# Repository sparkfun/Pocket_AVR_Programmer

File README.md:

Pocket AVR Programmer
=====================

[  
*Pocket AVR Programmer (PGM-09825)*](https://www.sparkfun.com/products/9825)

This is a simple to use USB AVR programmer, that works with ATmega168 and ATmega328 and should work well
with all the AVR micros supported by AVRDUDE.

Repository Contents
-------------------
* **/Enclosure** - 3D model of enclosure for this (.stl).
* **/Drivers** - Windows 7 drivers for use with this programmer. 
* **/Firmware** - Firmware that ships on the Pocket AVR Programmer.
* **/Hardware** - All Eagle design files (.brd, .sch).

Documentation
--------------
* **[Hookup Guide](https://learn.sparkfun.com/tutorials/pocket-avr-programmer-hookup-guide)** - Basic hookup guide for the Pocket AVR Programmer. 
* **[Installing an Arduino Bootloader](https://learn.sparkfun.com/tutorials/installing-an-arduino-bootloader)**  - Example of installing an Arduino bootloader on an Atmega328P-based microcontrollers (i.e. Arduino Uno and RedBoard Programmed with Arduino) through the Arduino IDE and command line using avrdude.

License Information
-------------------
The hardware is released under [Creative Commons Share-alike 3.0](http://creativecommons.org/licenses/by-sa/3.0/).
The firmware is based off of:
* [USBtiny](http://dicks.home.xs4all.nl/avr/usbtiny/index.html) by Dick Streefland
* [USBtinyISP](http://www.ladyada.net/make/usbtinyisp/) by Limor Fried and is a collaboration with Limor Fried currently.

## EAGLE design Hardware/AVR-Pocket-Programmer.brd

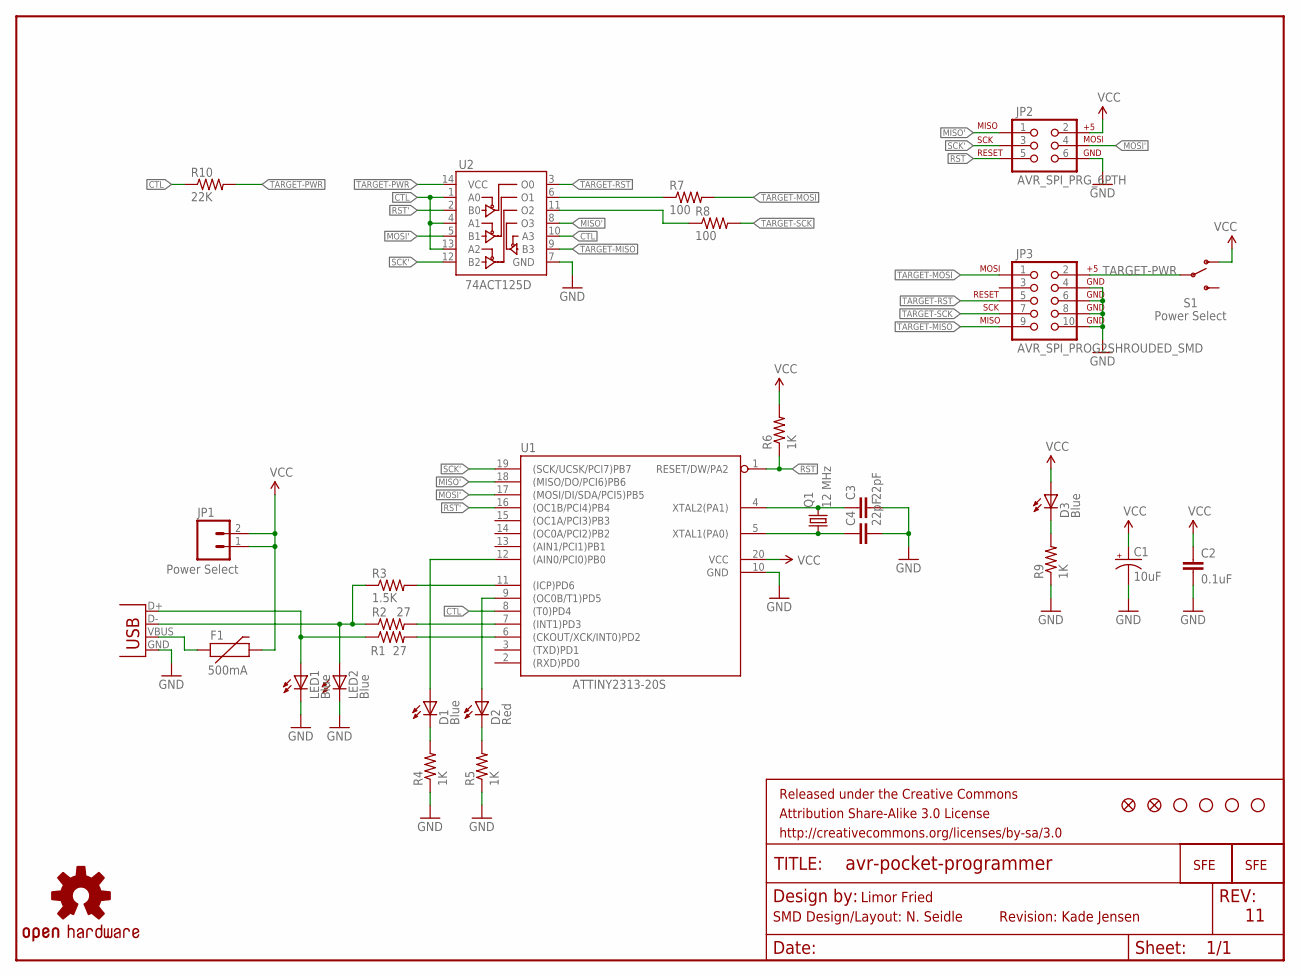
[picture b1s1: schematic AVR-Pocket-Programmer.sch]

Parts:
C1: 10uF; EIA3216
C2: 0.1uF; 0603-CAP
C3, C4: 22pF; 0603-CAP
D1, D3: Blue; LED-0603
D2: Red; LED-0603
F1: 500mA; PTC-1206-WIDE
FRAME1: FRAME-LETTER; CREATIVE_COMMONS
JP1: Power Select; 1X02
JP2: AVR_SPI_PRG_6PTH; 2X3
JP3: AVR_SPI_PROG2SHROUDED_SMD; 2X5-SHROUDED_SMD
LED1, LED2: Blue; LED-0603
LOGO1: OSHW-LOGOM; OSHW-LOGO-M
Q1: 12 MHz; CRYSTAL-SMD-5X3
R1, R2: 27; 0603-RES
R3: 1.5K; 0603-RES
R4, R5, R6, R9: 1K; 0603-RES
R7, R8: 100; 0603-RES
R10: 22K; 0603-RES
S1: Power Select; AYZ0202
U1: ATTINY2313-20S; SO20L
U2: 74ACT125D; SO014
U$1, U$3, U$4, U$5: STAND-OFF
U$2: LOGO-SFESK; SFE-LOGO-FLAME
U$6, U$7: FIDUCIAL1X2; FIDUCIAL-1X2
U$8: LOGO-SFENEW; SFE-NEW-WEBLOGO
X2: USBSMD; USB-MINIB

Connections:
CTL: R10.1, U1.8 ((T0)PD4), U2.1 (A0), U2.4 (A1), U2.10 (A3), U2.13 (A2)
D+: LED1.A, R1.1, X2.D+
D-: LED2.A, R2.1, R3.1, X2.D-
GND: C1.C (-), C2.2, C3.2, C4.2, JP2.6, JP3.4, JP3.6, JP3.8, JP3.10, LED1.C, LED2.C, R4.1, R5.1, R9.1, U1.10 (GND), U2.7 (GND), X2.GND
MISO': JP2.1, U1.18 ((MISO/DO/PCI6)PB6), U2.8 (O3)
MOSI': JP2.4, U1.17 ((MOSI/DI/SDA/PCI5)PB5), U2.5 (B1)
unnamed: R3.2, U1.11 ((ICP)PD6)
unnamed: D2.A, U1.9 ((OC0B/T1)PD5)
unnamed: D3.C, R9.2
unnamed: F1.1, X2.VBUS
unnamed: C3.1, Q1.3 (2), U1.4 (XTAL2(PA1))
unnamed: C4.1, Q1.1, U1.5 (XTAL1(PA0))
unnamed: D1.A, U1.12 ((AIN0/PCI0)PB0)
unnamed: D1.C, R4.2
unnamed: D2.C, R5.2
unnamed: R7.1, U2.6 (O1)
unnamed: R8.1, U2.11 (O2)
PD+: R1.2, U1.6 ((CKOUT/XCK/INT0)PD2)
PD-: R2.2, U1.7 ((INT1)PD3)
RST: JP2.5, R6.1, U1.1 (RESET/DW/PA2)
RST': U1.16 ((OC1B/PCI4)PB4), U2.2 (B0)
SCK': JP2.3, U1.19 ((SCK/UCSK/PCI7)PB7), U2.12 (B2)
TARGET-MISO: JP3.9, U2.9 (B3)
TARGET-MOSI: JP3.1, R7.2
TARGET-PWR: JP3.2, R10.2, S1.2, U2.14 (VCC)
TARGET-RST: JP3.5, U2.3 (O0)
TARGET-SCK: JP3.7, R8.2
VCC: C1.A (+), C2.1, D3.A, F1.2, JP1.1, JP1.2, JP2.2, R6.2, S1.1 (O), U1.20 (VCC)

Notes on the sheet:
Limor Fried
SMD Design/Layout: N. Seidle
Revision: Kade Jensen

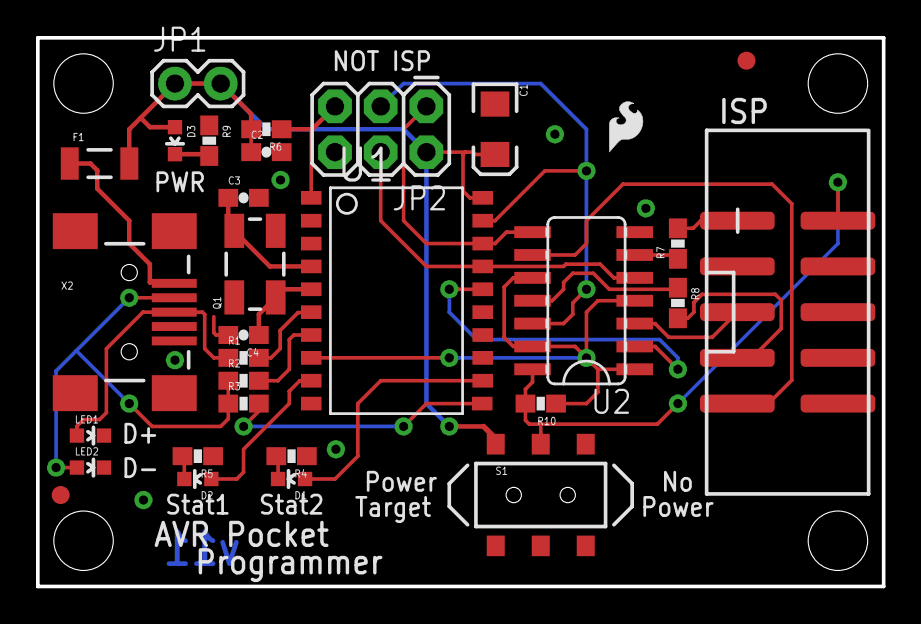
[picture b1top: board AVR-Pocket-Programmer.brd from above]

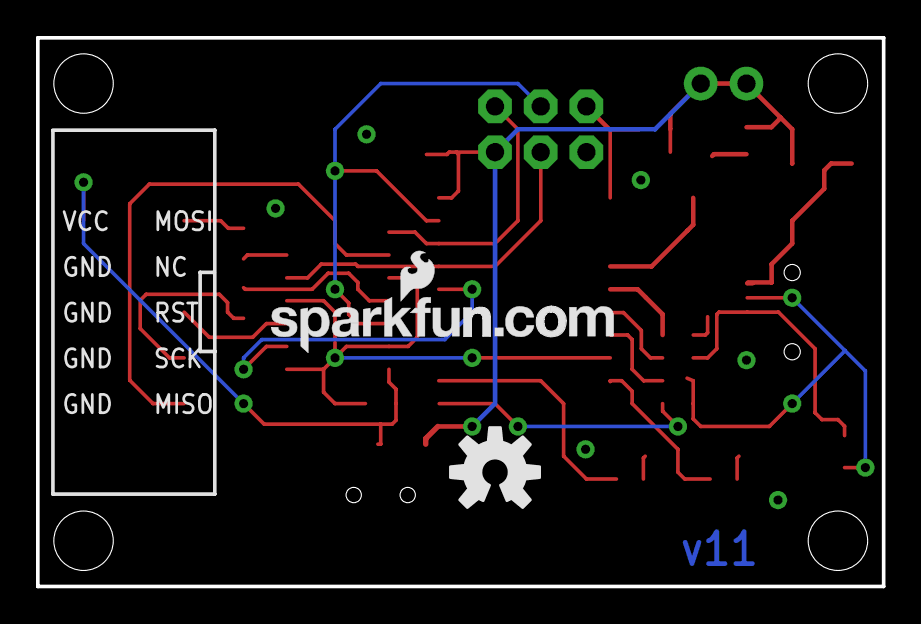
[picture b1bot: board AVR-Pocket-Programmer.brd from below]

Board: 2 copper layers, 47.0 x 30.5 mm, 38 parts (2 on the bottom side), 28 nets.

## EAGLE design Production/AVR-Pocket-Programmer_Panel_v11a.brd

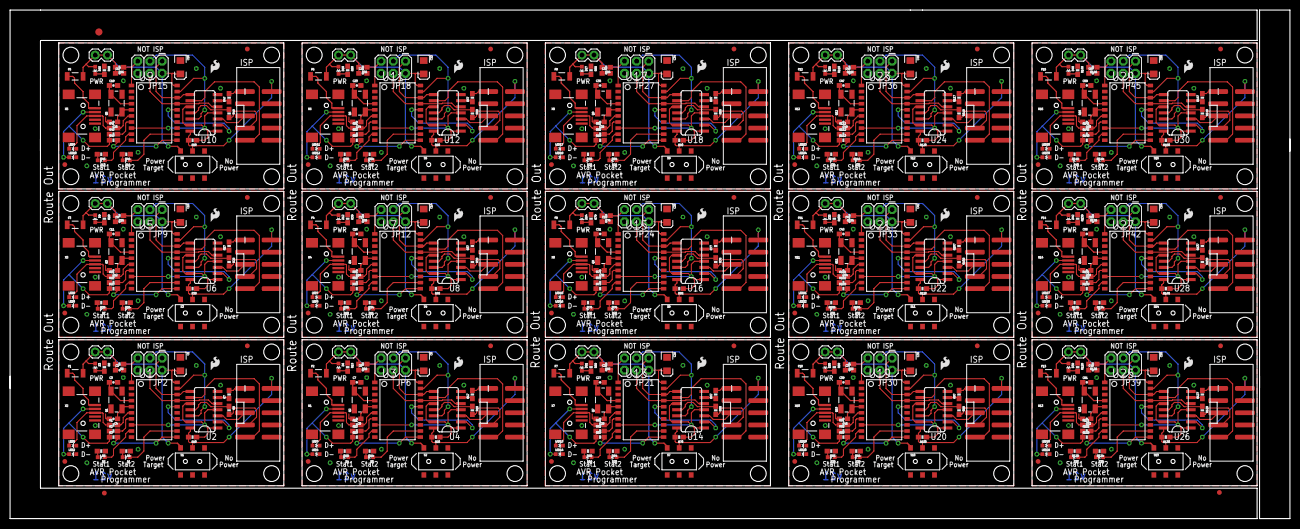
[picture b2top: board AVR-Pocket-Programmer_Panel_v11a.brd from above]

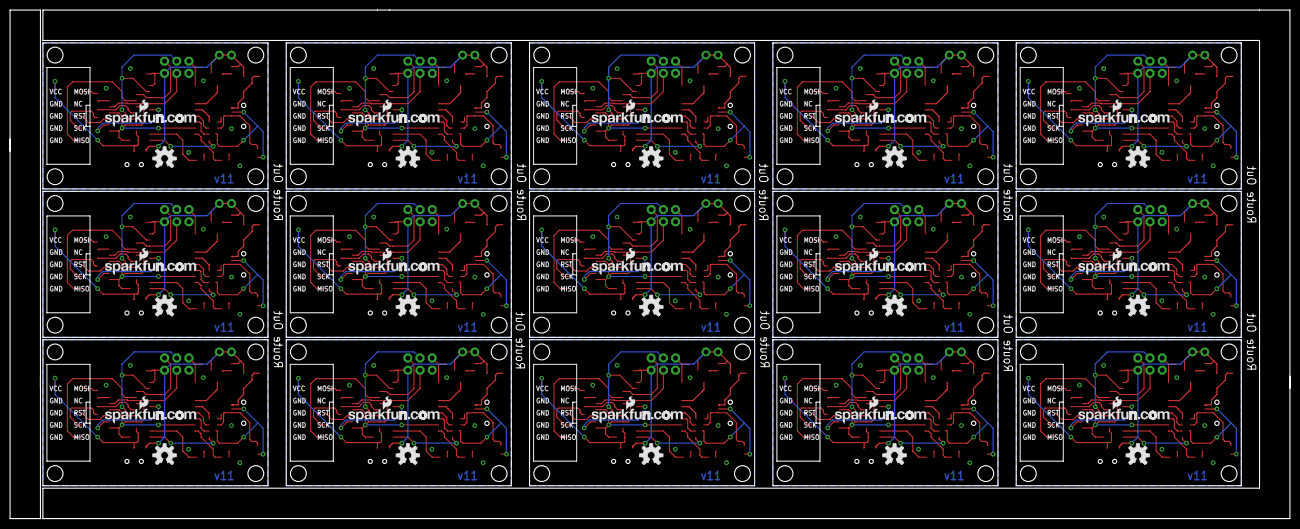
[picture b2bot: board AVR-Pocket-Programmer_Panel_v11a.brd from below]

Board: 2 copper layers, 267.2 x 106.2 mm, 558 parts (30 on the bottom side), 420 nets.

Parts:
C1, C6, C10, C14, C18, C22, C26, C30, C34, C38, C42, C46, C50, C54, C58: 10uF; EIA3216
C2, C5, C9, C13, C17, C21, C25, C29, C33, C37, C41, C45, C49, C53, C57: 0.1uF; 0603-CAP
C3, C4, C7, C8, C11, C12, C15, C16, C19, C20, C23, C24, C27, C28, C31, C32, C35, C36, C39, C40, C43, C44, C47, C48, C51, C52, C55, C56, C59, C60: 22pF; 0603-CAP
D1, D3, D5, D6, D8, D9, D11, D12, D14, D15, D17, D18, D20, D21, D23, D24, D26, D27, D29, D30, D32, D33, D35, D36, D38, D39, D41, D42, D44, D45: Blue; LED-0603
D2, D4, D7, D10, D13, D16, D19, D22, D25, D28, D31, D34, D37, D40, D43: Red; LED-0603
E$1: FIDUCIAL-1.5X3
E$2, E$7: FIDUCIAL-1X2
F1, F2, F3, F4, F5, F6, F7, F8, F9, F10, F11, F12, F13, F14, F15: 500mA; PTC-1206-WIDE
JP1, JP4, JP7, JP10, JP13, JP16, JP19, JP22, JP25, JP28, JP31, JP34, JP37, JP40, JP43: Power Select; 1X02
JP2, JP6, JP9, JP12, JP15, JP18, JP21, JP24, JP27, JP30, JP33, JP36, JP39, JP42, JP45: AVR_SPI_PRG_6PTH; 2X3
JP3, JP5, JP8, JP11, JP14, JP17, JP20, JP23, JP26, JP29, JP32, JP35, JP38, JP41, JP44: AVR_SPI_PROG2SHROUDED_SMD; 2X5-SHROUDED_SMD
LED1, LED2, LED3, LED4, LED5, LED6, LED7, LED8, LED9, LED10, LED11, LED12, LED13, LED14, LED15, LED16, LED17, LED18, LED19, LED20, LED21, LED22, LED23, LED24, LED25, LED26, LED27, LED28, LED29, LED30: Blue; LED-0603
LOGO1, LOGO2, LOGO3, LOGO4, LOGO5, LOGO6, LOGO7, LOGO8, LOGO9, LOGO10, LOGO11, LOGO12, LOGO13, LOGO14, LOGO15: OSHW-LOGOM; OSHW-LOGO-M
Q1, Q2, Q3, Q4, Q5, Q6, Q7, Q8, Q9, Q10, Q11, Q12, Q13, Q14, Q15: 12 MHz; CRYSTAL-SMD-5X3
R1, R2, R11, R12, R21, R22, R31, R32, R41, R42, R51, R52, R61, R62, R71, R72, R81, R82, R91, R92, R101, R102, R111, R112, R121, R122, R131, R132, R141, R142: 27; 0603-RES
R3, R13, R23, R33, R43, R53, R63, R73, R83, R93, R103, R113, R123, R133, R143: 1.5K; 0603-RES
R4, R5, R6, R9, R14, R15, R16, R19, R24, R25, R26, R29, R34, R35, R36, R39, R44, R45, R46, R49, R54, R55, R56, R59, R64, R65, R66, R69, R74, R75, R76, R79, R84, R85, R86, R89, R94, R95, R96, R99, R104, R105, R106, R109, R114, R115, R116, R119, R124, R125, R126, R129, R134, R135, R136, R139, R144, R145, R146, R149: 1K; 0603-RES
R7, R8, R17, R18, R27, R28, R37, R38, R47, R48, R57, R58, R67, R68, R77, R78, R87, R88, R97, R98, R107, R108, R117, R118, R127, R128, R137, R138, R147, R148: 100; 0603-RES
R10, R20, R30, R40, R50, R60, R70, R80, R90, R100, R110, R120, R130, R140, R150: 22K; 0603-RES
S1, S2, S3, S4, S5, S6, S7, S8, S9, S10, S11, S12, S13, S14, S15: Power Select; AYZ0202
U1, U3, U5, U7, U9, U11, U13, U15, U17, U19, U21, U23, U25, U27, U29: ATTINY2313-20S; SO20L
U2, U4, U6, U8, U10, U12, U14, U16, U18, U20, U22, U24, U26, U28, U30: 74ACT125D; SO014
U$1, U$3, U$4, U$5, U$9, U$10, U$11, U$12, U$17, U$18, U$19, U$20, U$25, U$26, U$27, U$28, U$33, U$34, U$35, U$36, U$41, U$42, U$43, U$44, U$49, U$50, U$51, U$52, U$57, U$58, U$59, U$60, U$65, U$66, U$67, U$68, U$73, U$74, U$75, U$76, U$81, U$82, U$83, U$84, U$89, U$90, U$91, U$92, U$97, U$98, U$99, U$100, U$105, U$106, U$107, U$108, U$113, U$114, U$115, U$116: STAND-OFF
U$2, U$16, U$24, U$32, U$40, U$48, U$56, U$64, U$72, U$80, U$88, U$96, U$104, U$112, U$120: LOGO-SFESK; SFE-LOGO-FLAME
U$6, U$7, U$13, U$14, U$21, U$22, U$29, U$30, U$37, U$38, U$45, U$46, U$53, U$54, U$61, U$62, U$69, U$70, U$77, U$78, U$85, U$86, U$93, U$94, U$101, U$102, U$109, U$110, U$117, U$118: FIDUCIAL1X2; FIDUCIAL-1X2
U$8, U$15, U$23, U$31, U$39, U$47, U$55, U$63, U$71, U$79, U$87, U$95, U$103, U$111, U$119: LOGO-SFENEW; SFE-NEW-WEBLOGO
X1, X2, X3, X4, X5, X6, X7, X8, X9, X10, X11, X12, X13, X14, X15: USBSMD; USB-MINIB

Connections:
CTL: R10.1, U1.8, U2.1, U2.4, U2.10, U2.13
CTL1: R20.1, U3.8, U4.1, U4.4, U4.10, U4.13
CTL2: R30.1, U5.8, U6.1, U6.4, U6.10, U6.13
CTL3: R40.1, U7.8, U8.1, U8.4, U8.10, U8.13
CTL4: R50.1, U9.8, U10.1, U10.4, U10.10, U10.13
CTL5: R60.1, U11.8, U12.1, U12.4, U12.10, U12.13
CTL6: R70.1, U13.8, U14.1, U14.4, U14.10, U14.13
CTL7: R80.1, U15.8, U16.1, U16.4, U16.10, U16.13
CTL8: R90.1, U17.8, U18.1, U18.4, U18.10, U18.13
CTL9: R100.1, U19.8, U20.1, U20.4, U20.10, U20.13
CTL10: R110.1, U21.8, U22.1, U22.4, U22.10, U22.13
CTL11: R120.1, U23.8, U24.1, U24.4, U24.10, U24.13
CTL12: R130.1, U25.8, U26.1, U26.4, U26.10, U26.13
CTL13: R140.1, U27.8, U28.1, U28.4, U28.10, U28.13
CTL14: R150.1, U29.8, U30.1, U30.4, U30.10, U30.13
D+: LED1.A, R1.1, X2.D+
D+1: LED3.A, R11.1, X1.D+
D+2: LED5.A, R21.1, X3.D+
D+3: LED7.A, R31.1, X4.D+
D+4: LED9.A, R41.1, X5.D+
D+5: LED11.A, R51.1, X6.D+
D+6: LED13.A, R61.1, X7.D+
D+7: LED15.A, R71.1, X8.D+
D+8: LED17.A, R81.1, X9.D+
D+9: LED19.A, R91.1, X10.D+
D+10: LED21.A, R101.1, X11.D+
D+11: LED23.A, R111.1, X12.D+
D+12: LED25.A, R121.1, X13.D+
D+13: LED27.A, R131.1, X14.D+
D+14: LED29.A, R141.1, X15.D+
D-: LED2.A, R2.1, R3.1, X2.D-
D-1: LED4.A, R12.1, R13.1, X1.D-
D-2: LED6.A, R22.1, R23.1, X3.D-
D-3: LED8.A, R32.1, R33.1, X4.D-
D-4: LED10.A, R42.1, R43.1, X5.D-
D-5: LED12.A, R52.1, R53.1, X6.D-
D-6: LED14.A, R62.1, R63.1, X7.D-
D-7: LED16.A, R72.1, R73.1, X8.D-
D-8: LED18.A, R82.1, R83.1, X9.D-
D-9: LED20.A, R92.1, R93.1, X10.D-
D-10: LED22.A, R102.1, R103.1, X11.D-
D-11: LED24.A, R112.1, R113.1, X12.D-
D-12: LED26.A, R122.1, R123.1, X13.D-
D-13: LED28.A, R132.1, R133.1, X14.D-
D-14: LED30.A, R142.1, R143.1, X15.D-
GND: C1.C, C2.2, C3.2, C4.2, JP2.6, JP3.4, JP3.6, JP3.8, JP3.10, LED1.C, LED2.C, R4.1, R5.1, R9.1, U1.10, U2.7, X2.GND
GND1: C5.2, C6.C, C7.2, C8.2, JP5.4, JP5.6, JP5.8, JP5.10, JP6.6, LED3.C, LED4.C, R14.1, R15.1, R19.1, U3.10, U4.7, X1.GND
GND2: C9.2, C10.C, C11.2, C12.2, JP8.4, JP8.6, JP8.8, JP8.10, JP9.6, LED5.C, LED6.C, R24.1, R25.1, R29.1, U5.10, U6.7, X3.GND
GND3: C13.2, C14.C, C15.2, C16.2, JP11.4, JP11.6, JP11.8, JP11.10, JP12.6, LED7.C, LED8.C, R34.1, R35.1, R39.1, U7.10, U8.7, X4.GND
GND4: C17.2, C18.C, C19.2, C20.2, JP14.4, JP14.6, JP14.8, JP14.10, JP15.6, LED9.C, LED10.C, R44.1, R45.1, R49.1, U9.10, U10.7, X5.GND
GND5: C21.2, C22.C, C23.2, C24.2, JP17.4, JP17.6, JP17.8, JP17.10, JP18.6, LED11.C, LED12.C, R54.1, R55.1, R59.1, U11.10, U12.7, X6.GND
GND6: C25.2, C26.C, C27.2, C28.2, JP20.4, JP20.6, JP20.8, JP20.10, JP21.6, LED13.C, LED14.C, R64.1, R65.1, R69.1, U13.10, U14.7, X7.GND
GND7: C29.2, C30.C, C31.2, C32.2, JP23.4, JP23.6, JP23.8, JP23.10, JP24.6, LED15.C, LED16.C, R74.1, R75.1, R79.1, U15.10, U16.7, X8.GND
GND8: C33.2, C34.C, C35.2, C36.2, JP26.4, JP26.6, JP26.8, JP26.10, JP27.6, LED17.C, LED18.C, R84.1, R85.1, R89.1, U17.10, U18.7, X9.GND
GND9: C37.2, C38.C, C39.2, C40.2, JP29.4, JP29.6, JP29.8, JP29.10, JP30.6, LED19.C, LED20.C, R94.1, R95.1, R99.1, U19.10, U20.7, X10.GND
GND10: C41.2, C42.C, C43.2, C44.2, JP32.4, JP32.6, JP32.8, JP32.10, JP33.6, LED21.C, LED22.C, R104.1, R105.1, R109.1, U21.10, U22.7, X11.GND
GND11: C45.2, C46.C, C47.2, C48.2, JP35.4, JP35.6, JP35.8, JP35.10, JP36.6, LED23.C, LED24.C, R114.1, R115.1, R119.1, U23.10, U24.7, X12.GND
GND12: C49.2, C50.C, C51.2, C52.2, JP38.4, JP38.6, JP38.8, JP38.10, JP39.6, LED25.C, LED26.C, R124.1, R125.1, R129.1, U25.10, U26.7, X13.GND
GND13: C53.2, C54.C, C55.2, C56.2, JP41.4, JP41.6, JP41.8, JP41.10, JP42.6, LED27.C, LED28.C, R134.1, R135.1, R139.1, U27.10, U28.7, X14.GND
GND14: C57.2, C58.C, C59.2, C60.2, JP44.4, JP44.6, JP44.8, JP44.10, JP45.6, LED29.C, LED30.C, R144.1, R145.1, R149.1, U29.10, U30.7, X15.GND
MISO': JP2.1, U1.18, U2.8
MISO'1: JP6.1, U3.18, U4.8
MISO'2: JP9.1, U5.18, U6.8
MISO'3: JP12.1, U7.18, U8.8
MISO'4: JP15.1, U9.18, U10.8
MISO'5: JP18.1, U11.18, U12.8
MISO'6: JP21.1, U13.18, U14.8
MISO'7: JP24.1, U15.18, U16.8
MISO'8: JP27.1, U17.18, U18.8
MISO'9: JP30.1, U19.18, U20.8
MISO'10: JP33.1, U21.18, U22.8
MISO'11: JP36.1, U23.18, U24.8
MISO'12: JP39.1, U25.18, U26.8
MISO'13: JP42.1, U27.18, U28.8
MISO'14: JP45.1, U29.18, U30.8
MOSI': JP2.4, U1.17, U2.5
MOSI'1: JP6.4, U3.17, U4.5
MOSI'2: JP9.4, U5.17, U6.5
MOSI'3: JP12.4, U7.17, U8.5
MOSI'4: JP15.4, U9.17, U10.5
MOSI'5: JP18.4, U11.17, U12.5
MOSI'6: JP21.4, U13.17, U14.5
MOSI'7: JP24.4, U15.17, U16.5
MOSI'8: JP27.4, U17.17, U18.5
MOSI'9: JP30.4, U19.17, U20.5
MOSI'10: JP33.4, U21.17, U22.5
MOSI'11: JP36.4, U23.17, U24.5
MOSI'12: JP39.4, U25.17, U26.5
MOSI'13: JP42.4, U27.17, U28.5
MOSI'14: JP45.4, U29.17, U30.5
unnamed: R3.2, U1.11
unnamed: D2.A, U1.9
unnamed: D3.C, R9.2
unnamed: F1.1, X2.VBUS
unnamed: C3.1, Q1.3, U1.4
unnamed: C4.1, Q1.1, U1.5
unnamed: R13.2, U3.11
unnamed: D4.A, U3.9
unnamed: D5.A, U3.12
unnamed: D5.C, R14.2
unnamed: D4.C, R15.2
unnamed: R17.1, U4.6
unnamed: R18.1, U4.11
unnamed: D6.C, R19.2
unnamed: F2.1, X1.VBUS
unnamed: C7.1, Q2.3, U3.4
unnamed: D1.A, U1.12
unnamed: D1.C, R4.2
unnamed: D2.C, R5.2
unnamed: C8.1, Q2.1, U3.5
unnamed: R23.2, U5.11
unnamed: R7.1, U2.6
unnamed: D7.A, U5.9
unnamed: D8.A, U5.12
unnamed: R8.1, U2.11
unnamed: D8.C, R24.2
unnamed: D7.C, R25.2
unnamed: R27.1, U6.6
unnamed: R28.1, U6.11
unnamed: D9.C, R29.2
unnamed: F3.1, X3.VBUS
unnamed: C11.1, Q3.3, U5.4
unnamed: C12.1, Q3.1, U5.5
unnamed: R33.2, U7.11
unnamed: D10.A, U7.9
unnamed: D11.A, U7.12
unnamed: D11.C, R34.2
unnamed: D10.C, R35.2
unnamed: R37.1, U8.6
unnamed: R38.1, U8.11
unnamed: D12.C, R39.2
unnamed: F4.1, X4.VBUS
unnamed: C15.1, Q4.3, U7.4
unnamed: C16.1, Q4.1, U7.5
unnamed: R43.2, U9.11
unnamed: D13.A, U9.9
unnamed: D14.A, U9.12
unnamed: D14.C, R44.2
unnamed: D13.C, R45.2
unnamed: R47.1, U10.6
unnamed: R48.1, U10.11
unnamed: D15.C, R49.2
unnamed: F5.1, X5.VBUS
unnamed: C19.1, Q5.3, U9.4
unnamed: C20.1, Q5.1, U9.5
unnamed: R53.2, U11.11
unnamed: D16.A, U11.9
unnamed: D17.A, U11.12
unnamed: D17.C, R54.2
unnamed: D16.C, R55.2
unnamed: R57.1, U12.6
unnamed: R58.1, U12.11
unnamed: D18.C, R59.2
unnamed: F6.1, X6.VBUS
unnamed: C23.1, Q6.3, U11.4
unnamed: C24.1, Q6.1, U11.5
unnamed: R63.2, U13.11
unnamed: D19.A, U13.9
unnamed: D20.A, U13.12
unnamed: D20.C, R64.2
unnamed: D19.C, R65.2
unnamed: R67.1, U14.6
unnamed: R68.1, U14.11
unnamed: D21.C, R69.2
unnamed: F7.1, X7.VBUS
unnamed: C27.1, Q7.3, U13.4
unnamed: C28.1, Q7.1, U13.5
unnamed: R73.2, U15.11
unnamed: D22.A, U15.9
unnamed: D23.A, U15.12
unnamed: D23.C, R74.2
unnamed: D22.C, R75.2
unnamed: R77.1, U16.6
unnamed: R78.1, U16.11
unnamed: D24.C, R79.2
unnamed: F8.1, X8.VBUS
unnamed: C31.1, Q8.3, U15.4
unnamed: C32.1, Q8.1, U15.5
unnamed: R83.2, U17.11
unnamed: D25.A, U17.9
unnamed: D26.A, U17.12
unnamed: D26.C, R84.2
unnamed: D25.C, R85.2
unnamed: R87.1, U18.6
unnamed: R88.1, U18.11
unnamed: D27.C, R89.2
unnamed: F9.1, X9.VBUS
unnamed: C35.1, Q9.3, U17.4
unnamed: C36.1, Q9.1, U17.5
unnamed: R93.2, U19.11
unnamed: D28.A, U19.9
unnamed: D29.A, U19.12
unnamed: D29.C, R94.2
unnamed: D28.C, R95.2
unnamed: R97.1, U20.6
unnamed: R98.1, U20.11
unnamed: D30.C, R99.2
unnamed: F10.1, X10.VBUS
unnamed: C39.1, Q10.3, U19.4
unnamed: C40.1, Q10.1, U19.5
unnamed: R103.2, U21.11
unnamed: D31.A, U21.9
unnamed: D32.A, U21.12
unnamed: D32.C, R104.2
unnamed: D31.C, R105.2
unnamed: R107.1, U22.6
unnamed: R108.1, U22.11
unnamed: D33.C, R109.2
unnamed: F11.1, X11.VBUS
unnamed: C43.1, Q11.3, U21.4
unnamed: C44.1, Q11.1, U21.5
unnamed: R113.2, U23.11
unnamed: D34.A, U23.9
unnamed: D35.A, U23.12
unnamed: D35.C, R114.2
unnamed: D34.C, R115.2
unnamed: R117.1, U24.6
unnamed: R118.1, U24.11
unnamed: D36.C, R119.2
unnamed: F12.1, X12.VBUS
unnamed: C47.1, Q12.3, U23.4
unnamed: C48.1, Q12.1, U23.5
unnamed: R123.2, U25.11
unnamed: D37.A, U25.9
unnamed: D38.A, U25.12
unnamed: D38.C, R124.2
unnamed: D37.C, R125.2
unnamed: R127.1, U26.6
unnamed: R128.1, U26.11
unnamed: D39.C, R129.2
unnamed: F13.1, X13.VBUS
unnamed: C51.1, Q13.3, U25.4
unnamed: C52.1, Q13.1, U25.5
unnamed: R133.2, U27.11
unnamed: D40.A, U27.9
unnamed: D41.A, U27.12
unnamed: D41.C, R134.2
unnamed: D40.C, R135.2
unnamed: R137.1, U28.6
unnamed: R138.1, U28.11
unnamed: D42.C, R139.2
unnamed: F14.1, X14.VBUS
unnamed: C55.1, Q14.3, U27.4
unnamed: C56.1, Q14.1, U27.5
unnamed: R143.2, U29.11
unnamed: D43.A, U29.9
unnamed: D44.A, U29.12
unnamed: D44.C, R144.2
unnamed: D43.C, R145.2
unnamed: R147.1, U30.6
unnamed: R148.1, U30.11
unnamed: D45.C, R149.2
unnamed: F15.1, X15.VBUS
unnamed: C59.1, Q15.3, U29.4
unnamed: C60.1, Q15.1, U29.5
PD+: R1.2, U1.6
PD+1: R11.2, U3.6
PD+2: R21.2, U5.6
PD+3: R31.2, U7.6
PD+4: R41.2, U9.6
PD+5: R51.2, U11.6
PD+6: R61.2, U13.6
PD+7: R71.2, U15.6
PD+8: R81.2, U17.6
PD+9: R91.2, U19.6
PD+10: R101.2, U21.6
PD+11: R111.2, U23.6
PD+12: R121.2, U25.6
PD+13: R131.2, U27.6
PD+14: R141.2, U29.6
PD-: R2.2, U1.7
PD-1: R12.2, U3.7
PD-2: R22.2, U5.7
PD-3: R32.2, U7.7
PD-4: R42.2, U9.7
PD-5: R52.2, U11.7
PD-6: R62.2, U13.7
PD-7: R72.2, U15.7
PD-8: R82.2, U17.7
PD-9: R92.2, U19.7
PD-10: R102.2, U21.7
PD-11: R112.2, U23.7
PD-12: R122.2, U25.7
PD-13: R132.2, U27.7
PD-14: R142.2, U29.7
RST: JP2.5, R6.1, U1.1
RST1: JP6.5, R16.1, U3.1
RST2: JP9.5, R26.1, U5.1
RST3: JP12.5, R36.1, U7.1
RST4: JP15.5, R46.1, U9.1
RST5: JP18.5, R56.1, U11.1
RST6: JP21.5, R66.1, U13.1
RST7: JP24.5, R76.1, U15.1
RST8: JP27.5, R86.1, U17.1
RST9: JP30.5, R96.1, U19.1
RST10: JP33.5, R106.1, U21.1
RST11: JP36.5, R116.1, U23.1
RST12: JP39.5, R126.1, U25.1
RST13: JP42.5, R136.1, U27.1
RST14: JP45.5, R146.1, U29.1
RST': U1.16, U2.2
RST'1: U3.16, U4.2
RST'2: U5.16, U6.2
RST'3: U7.16, U8.2
RST'4: U9.16, U10.2
RST'5: U11.16, U12.2
RST'6: U13.16, U14.2
RST'7: U15.16, U16.2
RST'8: U17.16, U18.2
RST'9: U19.16, U20.2
RST'10: U21.16, U22.2
RST'11: U23.16, U24.2
RST'12: U25.16, U26.2
RST'13: U27.16, U28.2
RST'14: U29.16, U30.2
SCK': JP2.3, U1.19, U2.12
SCK'1: JP6.3, U3.19, U4.12
SCK'2: JP9.3, U5.19, U6.12
SCK'3: JP12.3, U7.19, U8.12
SCK'4: JP15.3, U9.19, U10.12
SCK'5: JP18.3, U11.19, U12.12
SCK'6: JP21.3, U13.19, U14.12
SCK'7: JP24.3, U15.19, U16.12
SCK'8: JP27.3, U17.19, U18.12
SCK'9: JP30.3, U19.19, U20.12
SCK'10: JP33.3, U21.19, U22.12
SCK'11: JP36.3, U23.19, U24.12
SCK'12: JP39.3, U25.19, U26.12
SCK'13: JP42.3, U27.19, U28.12
SCK'14: JP45.3, U29.19, U30.12
TARGET-MISO: JP3.9, U2.9
TARGET-MISO1: JP5.9, U4.9
TARGET-MISO2: JP8.9, U6.9
TARGET-MISO3: JP11.9, U8.9
TARGET-MISO4: JP14.9, U10.9
TARGET-MISO5: JP17.9, U12.9
TARGET-MISO6: JP20.9, U14.9
TARGET-MISO7: JP23.9, U16.9
TARGET-MISO8: JP26.9, U18.9
TARGET-MISO9: JP29.9, U20.9
TARGET-MISO10: JP32.9, U22.9
TARGET-MISO11: JP35.9, U24.9
TARGET-MISO12: JP38.9, U26.9
TARGET-MISO13: JP41.9, U28.9
TARGET-MISO14: JP44.9, U30.9
TARGET-MOSI: JP3.1, R7.2
TARGET-MOSI1: JP5.1, R17.2
TARGET-MOSI2: JP8.1, R27.2
TARGET-MOSI3: JP11.1, R37.2
TARGET-MOSI4: JP14.1, R47.2
TARGET-MOSI5: JP17.1, R57.2
TARGET-MOSI6: JP20.1, R67.2
TARGET-MOSI7: JP23.1, R77.2
TARGET-MOSI8: JP26.1, R87.2
TARGET-MOSI9: JP29.1, R97.2
TARGET-MOSI10: JP32.1, R107.2
TARGET-MOSI11: JP35.1, R117.2
TARGET-MOSI12: JP38.1, R127.2
TARGET-MOSI13: JP41.1, R137.2
TARGET-MOSI14: JP44.1, R147.2
TARGET-PWR: JP3.2, R10.2, S1.2, U2.14
TARGET-PWR1: JP5.2, R20.2, S2.2, U4.14
TARGET-PWR2: JP8.2, R30.2, S3.2, U6.14
TARGET-PWR3: JP11.2, R40.2, S4.2, U8.14
TARGET-PWR4: JP14.2, R50.2, S5.2, U10.14
TARGET-PWR5: JP17.2, R60.2, S6.2, U12.14
TARGET-PWR6: JP20.2, R70.2, S7.2, U14.14
TARGET-PWR7: JP23.2, R80.2, S8.2, U16.14
TARGET-PWR8: JP26.2, R90.2, S9.2, U18.14
TARGET-PWR9: JP29.2, R100.2, S10.2, U20.14
TARGET-PWR10: JP32.2, R110.2, S11.2, U22.14
TARGET-PWR11: JP35.2, R120.2, S12.2, U24.14
TARGET-PWR12: JP38.2, R130.2, S13.2, U26.14
TARGET-PWR13: JP41.2, R140.2, S14.2, U28.14
TARGET-PWR14: JP44.2, R150.2, S15.2, U30.14
TARGET-RST: JP3.5, U2.3
TARGET-RST1: JP5.5, U4.3
TARGET-RST2: JP8.5, U6.3
TARGET-RST3: JP11.5, U8.3
TARGET-RST4: JP14.5, U10.3
TARGET-RST5: JP17.5, U12.3
TARGET-RST6: JP20.5, U14.3
TARGET-RST7: JP23.5, U16.3
TARGET-RST8: JP26.5, U18.3
TARGET-RST9: JP29.5, U20.3
TARGET-RST10: JP32.5, U22.3
TARGET-RST11: JP35.5, U24.3
TARGET-RST12: JP38.5, U26.3
TARGET-RST13: JP41.5, U28.3
TARGET-RST14: JP44.5, U30.3
TARGET-SCK: JP3.7, R8.2
TARGET-SCK1: JP5.7, R18.2
TARGET-SCK2: JP8.7, R28.2
TARGET-SCK3: JP11.7, R38.2
TARGET-SCK4: JP14.7, R48.2
TARGET-SCK5: JP17.7, R58.2
TARGET-SCK6: JP20.7, R68.2
TARGET-SCK7: JP23.7, R78.2
TARGET-SCK8: JP26.7, R88.2
TARGET-SCK9: JP29.7, R98.2
TARGET-SCK10: JP32.7, R108.2
TARGET-SCK11: JP35.7, R118.2
TARGET-SCK12: JP38.7, R128.2
TARGET-SCK13: JP41.7, R138.2
TARGET-SCK14: JP44.7, R148.2
VCC: C1.A, C2.1, D3.A, F1.2, JP1.1, JP1.2, JP2.2, R6.2, S1.1, U1.20
VCC1: C5.1, C6.A, D6.A, F2.2, JP4.1, JP4.2, JP6.2, R16.2, S2.1, U3.20
VCC2: C9.1, C10.A, D9.A, F3.2, JP7.1, JP7.2, JP9.2, R26.2, S3.1, U5.20
VCC3: C13.1, C14.A, D12.A, F4.2, JP10.1, JP10.2, JP12.2, R36.2, S4.1, U7.20
VCC4: C17.1, C18.A, D15.A, F5.2, JP13.1, JP13.2, JP15.2, R46.2, S5.1, U9.20
VCC5: C21.1, C22.A, D18.A, F6.2, JP16.1, JP16.2, JP18.2, R56.2, S6.1, U11.20
VCC6: C25.1, C26.A, D21.A, F7.2, JP19.1, JP19.2, JP21.2, R66.2, S7.1, U13.20
VCC7: C29.1, C30.A, D24.A, F8.2, JP22.1, JP22.2, JP24.2, R76.2, S8.1, U15.20
VCC8: C33.1, C34.A, D27.A, F9.2, JP25.1, JP25.2, JP27.2, R86.2, S9.1, U17.20
VCC9: C37.1, C38.A, D30.A, F10.2, JP28.1, JP28.2, JP30.2, R96.2, S10.1, U19.20
VCC10: C41.1, C42.A, D33.A, F11.2, JP31.1, JP31.2, JP33.2, R106.2, S11.1, U21.20
VCC11: C45.1, C46.A, D36.A, F12.2, JP34.1, JP34.2, JP36.2, R116.2, S12.1, U23.20
VCC12: C49.1, C50.A, D39.A, F13.2, JP37.1, JP37.2, JP39.2, R126.2, S13.1, U25.20
VCC13: C53.1, C54.A, D42.A, F14.2, JP40.1, JP40.2, JP42.2, R136.2, S14.1, U27.20
VCC14: C57.1, C58.A, D45.A, F15.2, JP43.1, JP43.2, JP45.2, R146.2, S15.1, U29.20

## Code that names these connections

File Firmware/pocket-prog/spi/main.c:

// ======================================================================
// Control a parallel port AVR programmer (avrdude type "bsd") via USB.
//
// Copyright 2006-2010 Dick Streefland
//
// This is free software, licensed under the terms of the GNU General
// Public License as published by the Free Software Foundation.
// ======================================================================

#include <avr/io.h>
#include "usb.h"

enum
{
	// Generic requests
	USBTINY_ECHO,		// echo test
	USBTINY_READ,		// read byte (wIndex:address)
	USBTINY_WRITE,		// write byte (wIndex:address, wValue:value)
	USBTINY_CLR,		// clear bit (wIndex:address, wValue:bitno)
	USBTINY_SET,		// set bit (wIndex:address, wValue:bitno)
	// Programming requests
	USBTINY_POWERUP,	// apply power (wValue:SCK-period, wIndex:RESET)
	USBTINY_POWERDOWN,	// remove power from chip
	USBTINY_SPI,		// issue SPI command (wValue:c1c0, wIndex:c3c2)
	USBTINY_POLL_BYTES,	// set poll bytes for write (wValue:p1p2)
	USBTINY_FLASH_READ,	// read flash (wIndex:address)
	USBTINY_FLASH_WRITE,	// write flash (wIndex:address, wValue:timeout)
	USBTINY_EEPROM_READ,	// read eeprom (wIndex:address)
	USBTINY_EEPROM_WRITE,	// write eeprom (wIndex:address, wValue:timeout)
};

// ----------------------------------------------------------------------
// Programmer output pins:
//	LED	PB0	(D0)
//	VCC	PB1	(D1)
//	VCC	PB2	(D2)
//	VCC	PB3	(D3)
//	RESET	PB5	(D5)
//	SCK	PB6	(D6)
//	MOSI	PB7	(D7)
// ----------------------------------------------------------------------
#define	PORT		PORTB
#define	DDR		DDRB
#define	POWER_MASK	0x0f
#define	RESET_MASK	(1 << 5)
#define	SCK_MASK	(1 << 6)
#define	MOSI_MASK	(1 << 7)

// ----------------------------------------------------------------------
// Programmer input pins:
//	MISO	PD3	(ACK)
// ----------------------------------------------------------------------
#define	PIN		PIND
#define	MISO_MASK	(1 << 3)

// ----------------------------------------------------------------------
// Local data
// ----------------------------------------------------------------------
static	byte_t		sck_period;	// SCK period in microseconds (1..250)
static	byte_t		poll1;		// first poll byte for write
static	byte_t		poll2;		// second poll byte for write
static	uint_t		address;	// read/write address
static	uint_t		timeout;	// write timeout in usec
static	byte_t		cmd0;		// current read/write command byte
static	byte_t		cmd[4];		// SPI command buffer
static	byte_t		res[4];		// SPI result buffer

// ----------------------------------------------------------------------
// Delay exactly <sck_period> times 0.5 microseconds (6 cycles).
// ----------------------------------------------------------------------
__attribute__((always_inline))
static	inline	void	delay ( void )
{
	asm volatile(
		"	mov	__tmp_reg__,%0	\n"
		"0:	rjmp	1f		\n"
		"1:	nop			\n"
		"	dec	__tmp_reg__	\n"
		"	brne	0b		\n"
		: : "r" (sck_period) );
}

// ----------------------------------------------------------------------
// Issue one SPI command.
// ----------------------------------------------------------------------
static	void	spi ( byte_t* cmd, byte_t* res )
{
	byte_t	i;
	byte_t	c;
	byte_t	r;
	byte_t	mask;

	for	( i = 0; i < 4; i++ )
	{
		c = *cmd++;
		r = 0;
		for	( mask = 0x80; mask; mask >>= 1 )
		{
			if	( c & mask )
			{
				PORT |= MOSI_MASK;
			}
			delay();
			PORT |= SCK_MASK;
			delay();
			r <<= 1;
			if	( PIN & MISO_MASK )
			{
				r++;
			}
			PORT &= ~ MOSI_MASK;
			PORT &= ~ SCK_MASK;
		}
		*res++ = r;
	}
}

// ----------------------------------------------------------------------
// Create and issue a read or write SPI command.
// ----------------------------------------------------------------------
static	void	spi_rw ( void )
{
	uint_t	a;

	a = address++;
	if	( cmd0 & 0x80 )
	{	// eeprom
		a <<= 1;
	}
	cmd[0] = cmd0;
	if	( a & 1 )
	{
		cmd[0] |= 0x08;
	}
	cmd[1] = a >> 9;
	cmd[2] = a >> 1;
	spi( cmd, res );
}

// ----------------------------------------------------------------------
// Handle a non-standard SETUP packet.
// ----------------------------------------------------------------------
extern	byte_t	usb_setup ( byte_t data[8] )
{
	byte_t	bit;
	byte_t	mask;
	byte_t*	addr;
	byte_t	req;

	// Generic requests
	req = data[1];
	if	( req == USBTINY_ECHO )
	{
		return 8;
	}
	addr = (byte_t*) (int) data[4];
	if	( req == USBTINY_READ )
	{
		data[0] = *addr;
		return 1;
	}
	if	( req == USBTINY_WRITE )
	{
		*addr = data[2];
		return 0;
	}
	bit = data[2] & 7;
	mask = 1 << bit;
	if	( req == USBTINY_CLR )
	{
		*addr &= ~ mask;
		return 0;
	}
	if	( req == USBTINY_SET )
	{
		*addr |= mask;
		return 0;
	}

	// Programming requests
	if	( req == USBTINY_POWERUP )
	{
		sck_period = data[2];
		mask = POWER_MASK;
		if	( data[4] )
		{
			mask |= RESET_MASK;
		}
		DDR  = 0xff;
		PORT = mask;
		return 0;
	}
	if	( req == USBTINY_POWERDOWN )
	{
		PORT |= RESET_MASK;
		PORT = 0x00;
		DDR  = 0x00;
		return 0;
	}
	if	( ! PORT )
	{
		return 0;
	}
	if	( req == USBTINY_SPI )
	{
		spi( data + 2, data + 0 );
		return 4;
	}
	if	( req == USBTINY_POLL_BYTES )
	{
		poll1 = data[2];
		poll2 = data[3];
		return 0;
	}
	address = * (uint_t*) & data[4];
	if	( req == USBTINY_FLASH_READ )
	{
		cmd0 = 0x20;
		return 0xff;	// usb_in() will be called to get the data
	}
	if	( req == USBTINY_EEPROM_READ )
	{
		cmd0 = 0xa0;
		return 0xff;	// usb_in() will be called to get the data
	}
	timeout = * (uint_t*) & data[2];
	if	( req == USBTINY_FLASH_WRITE )
	{
		cmd0 = 0x40;
		return 0;	// data will be received by usb_out()
	}
	if	( req == USBTINY_EEPROM_WRITE )
	{
		cmd0 = 0xc0;
		return 0;	// data will be received by usb_out()
	}
	return 0;
}

// ----------------------------------------------------------------------
// Handle an IN packet.
// ----------------------------------------------------------------------
extern	byte_t	usb_in ( byte_t* data, byte_t len )
{
	byte_t	i;

	for	( i = 0; i < len; i++ )
	{
		spi_rw();
		data[i] = res[3];
	}
	return len;
}

// ----------------------------------------------------------------------
// Handle an OUT packet.
// ----------------------------------------------------------------------
extern	void	usb_out ( byte_t* data, byte_t len )
{
	byte_t	i;
	uint_t	usec;
	byte_t	r;

	for	( i = 0; i < len; i++ )
	{
		cmd[3] = data[i];
		spi_rw();
		cmd[0] ^= 0x60;	// turn write into read
		for	( usec = 0; usec < timeout; usec += 32 * sck_period )
		{	// when timeout > 0, poll until byte is written
			spi( cmd, res );
			r = res[3];
			if	( r == cmd[3] && r != poll1 && r != poll2 )
			{
				break;
			}
		}
	}
}

// ----------------------------------------------------------------------
// Main
// ----------------------------------------------------------------------
extern	int	main ( void )
{
	usb_init();
	for	( ;; )
	{
		usb_poll();
	}
}

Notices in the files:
parts and their libraries:
SparkFun-Aesthetics: Licensing: CC v3.0 Share-Alike You are welcome to use this library for commercial purposes.
SparkFun-Aesthetics: Released under the Creative Commons Attribution Share-Alike 3.0 License
